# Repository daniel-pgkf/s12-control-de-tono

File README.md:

**Español** · [English](#english)

# S12 — Enseñar electrónica a través de equipos de música

S12 es un proyecto para enseñar electrónica usando como material de estudio los **equipos de música**: efectos, pedales, amplificadores, guitarras. La premisa es que un pedal de distorsión, una perilla de tono o una etapa de ganancia no son ejemplos decorativos de la teoría de circuitos — son teoría de circuitos, en un objeto que el estudiante ya conoce, ya escucha y ya quiere entender.

El proyecto tiene dos componentes que se alimentan mutuamente:

- **Los cursos** — material pedagógico completo y replicable, diseñado por audiencia.
- **El FRA** — un analizador de respuesta en frecuencia, construido desde cero, que sirve para caracterizar los efectos que ya existen y los que construyen los estudiantes, y para tocarlos con una guitarra eléctrica.

---

## El programa y sus cursos

S12 no es un curso único: es un programa del que se van derivando cursos, cada uno con su audiencia y su equipo de entrada. Lo que se mantiene constante es el método — entrar por un equipo de música real, construir la intuición antes de la fórmula, y cerrar midiendo.

### Curso 1 — Control de Tono

**Audiencia:** estudiantes de primer semestre de ingeniería electrónica, sin conocimientos previos de electrónica.

**Equipo de entrada:** la perilla de tono de una guitarra eléctrica.

Este primer curso es el que da nombre al repositorio. Su punto de entrada es la perilla de tono porque es, probablemente, el circuito no trivial más accesible que existe: se gira con la mano y el resultado se escucha de inmediato.

Una perilla de tono es un filtro RC pasa-bajos. Es un potenciómetro — girarla cambia el valor de la resistencia (R), lo que desplaza la frecuencia de corte del filtro y modifica el timbre de la guitarra. El capacitor es fijo. Ese objeto cotidiano contiene, en su interior, los mismos principios que se usan para diseñar filtros de audio, sistemas de comunicación y circuitos de procesamiento de señales.

**Progresión temática:**

```
Divisor de voltaje → Ley de mallas → Superposición → Filtros RC → Diagramas de Bode
```

Cada concepto se introduce como extensión natural del anterior. Al final, la perilla de tono deja de ser un misterio: el estudiante sabe exactamente qué está cambiando cuando la gira y por qué eso afecta el sonido.

**Formato:**

- Máximo 1.5 horas por sesión
- Entre 3 y 6 sesiones en total
- Cierra con un proyecto integrador en el que los estudiantes construyen o modifican un filtro RC y escuchan el resultado en tiempo real

### Cursos siguientes

El resto del gear musical queda como territorio por recorrer: distorsión y recorte, etapas de ganancia, delay, las fuentes de alimentación de un amplificador. Cada uno entra por su propio equipo y apunta a su propia audiencia. El curso de la perilla de tono es **el diseño para primeros semestres**, no el alcance del programa.

---

## Filosofía pedagógica

**Mínima matemática, máxima intuición.**

La idea es la misma que sigue Veritasium o 3Blue1Brown: el efecto se muestra antes de explicarse, la intuición se construye antes de formalizarse. Las fórmulas llegan al final, como descripción de algo que ya se entiende — no como punto de partida.

Para lograrlo se usa un sistema de analogías físicas. En lugar de definir el voltaje como diferencia de potencial eléctrico, se introduce como una propiedad del espacio que hace que una pelota —el portador de carga— siempre ruede de lo alto a lo bajo. En lugar de memorizar que un capacitor "bloquea DC y pasa AC", se visualiza como un bloque elástico que responde distinto según qué tan rápido lleguen las señales.

Estas analogías son deliberadamente imperfectas: son herramientas para construir intuición, no definiciones formales. El objetivo es que cuando el estudiante vea la definición real, ya tenga algo concreto en la cabeza a qué anclarla.

Un principio atraviesa todo el material: la resistencia le cobra **energía** a la carga, no existencia. La pelota nunca desaparece — si se queda sin energía se detiene, pero sigue ahí. Eso ataca de raíz la idea de que "la corriente se gasta".

---

## El FRA

### Qué es

Un **Frequency Response Analyzer** (analizador de respuesta en frecuencia) es un instrumento que mide cómo una red de dos puertos modifica una señal en función de la frecuencia. La salida es un diagrama de Bode: magnitud en dB y fase en grados, trazados sobre el eje de frecuencia.

Este FRA cubre el rango de 20 Hz a 20 kHz — el espectro audible completo.

### Para qué existe

El FRA es el instrumento de caracterización del programa. Se le conecta un efecto —uno comercial, uno casero, o **uno desarrollado por los estudiantes**— y mide qué le hace a la señal. En modo pedal, además, ese mismo efecto se puede **tocar con una guitarra eléctrica** en tiempo real.

Eso es lo que cierra el ciclo: el estudiante construye un efecto, lo mide y le ve el Bode, y lo toca. Sin el FRA, un efecto propio se queda en "suena raro". Con el FRA se vuelve un circuito caracterizado.

De ahí sale una restricción de diseño que no es negociable: el DUT (*device under test*) tiene que ser **genérico e intercambiable**. Cualquier efecto de un estudiante debe poder entrar, no solo una red RC. El slot modular y los jacks de 1/4" son parte del propósito, no un detalle de empaque.

### Cómo funciona

La señal entra por un jack, se acondiciona, y llega al slot donde está conectado el DUT. Lo que hace al FRA un instrumento de medida y no solo una caja de paso es que **mide los dos lados del DUT a la vez**: la señal tal como entra y la señal tal como sale. Comparar esas dos capturas es lo que da la respuesta en frecuencia.

Un microcontrolador se encarga de la captura, del cálculo y de enviar los datos al PC, donde se visualizan.

### Modos de operación

**Modo Pedal**

La señal de la guitarra pasa en vivo por el DUT y sale por el jack de salida, hacia un parlante o un amplificador. Mientras tanto se monitorean entrada y salida, así que el músico escucha el efecto y ve su huella espectral al mismo tiempo.

**Modo Bode**

Se desconecta la guitarra y se excita el DUT con una señal generada internamente. Comparando lo que entra con lo que sale, se obtiene el diagrama de Bode completo del efecto, de forma automática.

La excitación es ruido blanco: como tiene espectro plano, golpea todas las frecuencias del rango a la vez y la respuesta completa se obtiene en una sola captura corta, en lugar de barrer frecuencia por frecuencia. La estimación usa el método de Welch y reporta la coherencia como indicador de confiabilidad, para saber en qué bandas la medida es de fiar. El procesamiento está validado en `FRA/codigos/ruido_blanco.ipynb`.

---

## Las presentaciones

### Formato general

Las presentaciones no son slides. Son escenas continuas con checkpoints controlados por teclado: el instructor avanza cuando el grupo está listo, ni más rápido ni más lento. Varias escenas son además **simuladores** que el instructor maneja en vivo — se abre y cierra el circuito, se sueltan cargas, se cambia la resistencia, se transforma el modelo físico en esquemático.

Cada sesión combina dos tipos de contenido animado:

**Manim CE (Python)** — animaciones matemáticas y técnicas: ondas, diagramas de Bode emergiendo, circuitos con flechas, transformaciones. Renderizadas a video.

**p5.js (JavaScript)** — simulaciones físicas interactivas: la carga viajando por el conductor, el aceite de la resistencia deformándose a su paso, el divisor de voltaje respondiendo en tiempo real. Corren directo en el browser.

Un player web propio combina los clips de Manim y los sketches de p5.js en una sola secuencia navegable, y comparte una paleta única entre ambos mundos para que no se note la costura.

### Secuencia de cada concepto

Para cualquier concepto del curso, la presentación sigue siempre el mismo orden:

1. **Demostración observable** — se muestra el fenómeno antes de nombrarlo
2. **Analogía física animada** — se construye la intuición con el modelo físico
3. **Transferencia al circuito** — se mapea la analogía al circuito real
4. **Formalización** — llega la fórmula, ya anclada a algo concreto
5. **Medición** — se verifica con el FRA

---

## Stack técnico

| Herramienta         | Uso                                              |
| ------------------- | ------------------------------------------------ |
| Python 3.12 + venv  | Base del proyecto                                |
| Manim CE v0.20.1    | Animaciones técnicas y matemáticas             |
| p5.js (vendorizado) | Simulaciones físicas interactivas en browser    |
| FFmpeg              | Renderizado de video                             |
| Jupyter             | Documentación pedagógica y análisis de señal |
| KiCad               | Diseño de la PCB del FRA                        |

---

## Estructura del repositorio

```
control-de-tono/
├── presentaciones/     # Animaciones Manim, sketches p5.js, player web
├── FRA/                # Hardware, firmware, software PC
├── compras/            # BOM y materiales
└── syllabus/           # Contenido del curso, notebooks pedagógicos
```

Para correr las presentaciones:

```bash
cd presentaciones
python servidor.py 8000
# luego abrir http://127.0.0.1:8000/player/
```

<br>

---

[Español](#espanol) · **English**

# S12 — Teaching electronics through music gear

S12 is a project for teaching electronics using **music gear** as the study material: effects, pedals, amplifiers, guitars. The premise is that a distortion pedal, a tone knob or a gain stage aren't decorative examples of circuit theory — they *are* circuit theory, embodied in an object the student already knows, already listens to, and already wants to understand.

The project has two components that feed each other:

- **The courses** — complete, reproducible teaching material, designed per audience.
- **The FRA** — a frequency response analyzer, built from scratch, used to characterize both existing effects and the ones students build, and to play them through an electric guitar.

---

## The program and its courses

S12 isn't a single course: it's a program that spawns courses, each with its own audience and its own entry-point piece of gear. What stays constant is the method — enter through a real piece of music gear, build intuition before the formula, and close the loop by measuring.

### Course 1 — Tone Control

**Audience:** first-semester electronic engineering students, with no prior background in electronics.

**Entry-point gear:** the tone knob of an electric guitar.

This first course is the one the repository is named after. Its entry point is the tone knob because it's arguably the most accessible non-trivial circuit there is: you turn it by hand and hear the result immediately.

A tone knob is an RC low-pass filter. It's a potentiometer — turning it changes the resistance (R), which shifts the filter's cutoff frequency and alters the guitar's timbre. The capacitor is fixed. That everyday object contains, inside it, the same principles used to design audio filters, communication systems and signal processing circuits.

**Topic progression:**

```
Voltage divider → Kirchhoff's voltage law → Superposition → RC filters → Bode plots
```

Each concept is introduced as a natural extension of the previous one. By the end, the tone knob stops being a mystery: the student knows exactly what changes when they turn it, and why that affects the sound.

**Format:**

- 1.5 hours per session, maximum
- 3 to 6 sessions total
- Closes with a capstone project where students build or modify an RC filter and hear the result in real time

### Later courses

The rest of the musical gear landscape is territory still to be covered: distortion and clipping, gain stages, delay, amplifier power supplies. Each one enters through its own piece of gear and targets its own audience. The tone knob course is **the design for first-semester students**, not the scope of the program.

---

## Teaching philosophy

**Minimum math, maximum intuition.**

The approach is the one Veritasium and 3Blue1Brown follow: show the effect before explaining it, build the intuition before formalizing it. Formulas arrive last, as a description of something already understood — not as the starting point.

To get there, the material uses a system of physical analogies. Instead of defining voltage as electric potential difference, it's introduced as a property of space that makes a ball — the charge carrier — always roll from high to low. Instead of memorizing that a capacitor "blocks DC and passes AC", it's visualized as an elastic block that responds differently depending on how fast the signals arrive.

These analogies are deliberately imperfect: they're tools for building intuition, not formal definitions. The goal is that when the student meets the real definition, they already have something concrete to anchor it to.

One principle runs through all the material: resistance charges the carrier **energy**, not existence. The ball never disappears — if it runs out of energy it stops, but it's still there. That attacks the "current gets used up" misconception at its root.

---

## The FRA

### What it is

A **Frequency Response Analyzer** is an instrument that measures how a two-port network modifies a signal as a function of frequency. The output is a Bode plot: magnitude in dB and phase in degrees, plotted against frequency.

This FRA covers 20 Hz to 20 kHz — the full audible spectrum.

### Why it exists

The FRA is the program's characterization instrument. You plug an effect into it — a commercial one, a homemade one, or **one developed by the students** — and it measures what that effect does to the signal. In pedal mode, that same effect can also be **played through an electric guitar** in real time.

That's what closes the loop: the student builds an effect, measures it and sees its Bode plot, and then plays it. Without the FRA, a homemade effect stays at "sounds weird". With the FRA it becomes a characterized circuit.

From this follows a non-negotiable design constraint: the DUT (device under test) must be **generic and swappable**. Any student's effect has to be able to go in, not just an RC network. The modular slot and the 1/4" jacks are part of the purpose, not a packaging detail.

### How it works

The signal comes in through a jack, gets conditioned, and reaches the slot where the DUT is connected. What makes the FRA a measuring instrument rather than just a box the signal passes through is that it **measures both sides of the DUT at once**: the signal as it goes in and the signal as it comes out. Comparing those two captures is what yields the frequency response.

A microcontroller handles capture, computation, and streaming the data to the PC, where it's visualized.

### Operating modes

**Pedal mode**

The guitar signal passes live through the DUT and out the output jack, into a speaker or an amplifier. Meanwhile input and output are monitored, so the player hears the effect and sees its spectral fingerprint at the same time.

**Bode mode**

The guitar is disconnected and the DUT is excited with an internally generated signal. Comparing what goes in with what comes out yields the effect's complete Bode plot, automatically.

The excitation is white noise: since its spectrum is flat, it hits every frequency in the range at once, so the full response comes from a single short capture instead of a frequency-by-frequency sweep. The estimate uses Welch's method and reports coherence as a confidence indicator, to tell which bands are trustworthy. The processing is validated in `FRA/codigos/ruido_blanco.ipynb`.

---

## The presentations

### General format

The presentations aren't slides. They're continuous scenes with keyboard-driven checkpoints: the instructor advances when the group is ready, no faster and no slower. Several scenes are also **simulators** the instructor drives live — opening and closing the circuit, releasing charges, swapping the resistance, morphing the physical model into a schematic.

Each session combines two kinds of animated content:

**Manim CE (Python)** — mathematical and technical animations: waveforms, Bode plots being drawn, circuits with annotation arrows, transformations. Rendered to video.

**p5.js (JavaScript)** — interactive physical simulations: the charge traveling down the conductor, the resistance's oil deforming as it passes, the voltage divider responding in real time. They run directly in the browser.

A custom web player stitches the Manim clips and p5.js sketches into a single navigable sequence, and shares one palette across both worlds so the seam doesn't show.

### Sequence for every concept

For any concept in the course, the presentation always follows the same order:

1. **Observable demonstration** — show the phenomenon before naming it
2. **Animated physical analogy** — build intuition with the physical model
3. **Transfer to the circuit** — map the analogy onto the real circuit
4. **Formalization** — the formula arrives, already anchored to something concrete
5. **Measurement** — verify it with the FRA

---

## Tech stack

| Tool                | Used for                                     |
| ------------------- | -------------------------------------------- |
| Python 3.12 + venv  | Project base                                 |
| Manim CE v0.20.1    | Technical and mathematical animations        |
| p5.js (vendored)    | Interactive physical simulations in-browser  |
| FFmpeg              | Video rendering                              |
| Jupyter             | Teaching documentation and signal analysis   |
| KiCad               | FRA PCB design                               |

---

## Repository layout

```
control-de-tono/
├── presentaciones/     # Manim animations, p5.js sketches, web player
├── FRA/                # Hardware, firmware, PC software
├── compras/            # BOM and materials
└── syllabus/           # Course content, teaching notebooks
```

To run the presentations:

```bash
cd presentaciones
python servidor.py 8000
# then open http://127.0.0.1:8000/player/
```

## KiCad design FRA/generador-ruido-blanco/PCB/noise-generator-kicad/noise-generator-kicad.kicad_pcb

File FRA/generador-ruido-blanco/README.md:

# Generador de ruido blanco — verificación de planicidad

Mide el espectro **real** del generador de ruido blanco del FRA, capturándolo por
la Scarlett 2i2. Es la contraparte física de [`../codigos/ruido_blanco.ipynb`](../codigos/ruido_blanco.ipynb),
que simula el ruido con `randn()` y establece la teoría.

## Cadena de medición

```
Generador ruido blanco → jack 1/4" → Scarlett 2i2 (line in) → USB → captura_planicidad.py
```

Antes de correr: phantom power **apagado**, ganancia ajustada sin clipping.

## El generador — diseño final

Fuente de ruido por **avalancha**: la juntura base-emisor del transistor en
inversa, polarizada por el 100K desde 12 V. Acople de 1 µF y pulldown de 100K
(pasaaltos en 1.6 Hz, bien debajo de la banda).

```
        12V
         │
        100K
         │        1µF                                            1K
  Q ─────●────────┤├────●──── [buffer] ── [G=15.5] ── [G=15.5] ── [buffer] ──/\/\── NOISE
  (BE en                │
   inversa)           100K
         │              │
        GND            GND
```

Cuatro amplificadores en **un solo TL074** (JFET, quad, GBW 3 MHz):

| Etapa | Función | Rf / R1 | Ganancia |
|---|---|---|---|
| 1 | buffer de entrada | — | 1 |
| 2 | ganancia, no inversor | 680k / 47k | 15.47 |
| 3 | ganancia, no inversor | 680k / 47k | 15.47 |
| 4 | buffer de salida | — | 1 |

**Ganancia total: 15.47² ≈ 239.** Entrada ~0.84 mV RMS → salida ~200 mV RMS,
que es nivel de humbucker (ver "Nivel de salida" abajo).

### Por qué la ganancia va repartida y no en una etapa

Esta es **la** decisión de diseño del circuito, y no es obvia. Un opamp no
entrega su ganancia a cualquier frecuencia: lo constante es el **producto**
ganancia-ancho de banda. El ancho de banda real de una etapa es `GBW / G`.

La primera versión eran `1 + 100k/680 = 148` en una sola etapa:

```
fc = 3 MHz / 148 = 20.3 kHz      →  el polo caía justo en el borde de la banda
```

Repartida en dos etapas de 15.47, cada una solo necesita `3 MHz / 15.47`:

```
fc_etapa  = 194 kHz
fc_total  = 194 kHz × √(2^(1/2) − 1) = 125 kHz
```

(El `fc_total` no es el de una etapa: al encadenar N polos iguales, el −3 dB
conjunto llega antes. Con N=2 el factor es 0.644.)

Error en 20 kHz: **−0.09 dB**, contra −2.95 dB de la versión de una etapa. Y eso
que la ganancia total *subió* de 148 a 239: repartida, sale gratis.

> **Honestidad sobre la causa:** el polo de GBW explica ~3 dB, pero la versión
> vieja medía ~19 dB de rango. El resto salía del nodo de 50 kΩ sin bufferear
> (y de un opamp viejo que nunca identificamos). Los dos cambios —repartir la
> ganancia y bufferear la entrada— se hicieron juntos, así que con una sola
> medición no se pueden separar. Ambos eran necesarios.

### Por qué los buffers

- **Entrada:** el nodo de ruido tiene 100k ‖ 100k = **50 kΩ** de impedancia. Con
  esa Z, cualquier capacidad parásita del protoboard forma su propio pasabajos,
  y un opamp bipolar además metería offset por corriente de polarización. El
  buffer JFET (Ib ≈ 30 pA) aísla el nodo y manda ese polo lejos.
- **Salida:** deja el generador con impedancia baja para manejar el cable sin
  que la capacidad se coma los agudos. El 1K en serie es protección.

> Si algún día se sube la ganancia, **repartirla** — no subir una etapa. Al
> triplicar G se te divide por tres el ancho de banda de esa etapa.

### Nivel de salida

Ajustado a **~200 mV RMS** para imitar una pastilla pasiva (humbucker típica:
150–350 mV RMS). Con ruido gaussiano se iguala el **RMS, no el Vpp** — los picos
del ruido son estadísticos y crecen con el tiempo de observación, así que no hay
un Vpp definido. Con factor de cresta ≈ 4 (12 dB), esos 200 mV dan picos de
~800 mV.

> **Cuidado al medir la entrada con osciloscopio:** los ~0.84 mV RMS del nodo de
> ruido están por debajo del piso de un scope típico. Si lees ~20 mV ahí, es casi
> seguro el ruido propio del instrumento, no la señal. La cuenta que cierra es:
> salida medida ÷ 239.

## Uso

```bash
python captura_planicidad.py --list     # ver dispositivos, identificar la Scarlett
python captura_planicidad.py            # captura 10 s y analiza (autodetecta Scarlett)
python captura_planicidad.py --device 3 --dur 10 --channel 1
python captura_planicidad.py --wav espectro_ruido.wav   # re-analizar sin recapturar
```

Cada captura guarda el audio crudo en `.wav` junto al `.png`, así se puede
re-analizar con otro `nperseg` sin volver a montar el setup.

## Qué hace

1. **Verifica clipping** antes de procesar — aborta si el pico llega a fondo de
   escala. Un factor de cresta bajo (< 8 dB) también delata clipping: el ruido
   gaussiano sano da ≈ 11–13 dB.
2. **PSD por Welch**, no FFT directa. Una sola ventana de ruido tiene ~5.6 dB de
   desviación por bin (chi² 2 gdl) — imposible distinguir la respuesta del
   generador de la varianza de la propia realización. Welch promedia ventanas
   solapadas y baja esa varianza.
3. **Métricas de planicidad** en 20 Hz – 20 kHz: nivel medio, desviación estándar,
   rango max-min y SFM.

## Antes de medir: poner la Scarlett a 48 kHz

Estado al 2026-07-14: la interfaz está configurada a **44.1 kHz** en Windows, y
el script aborta con instrucciones si se pide 48 kHz. Conviene cambiarla:

> Panel de control de sonido → Grabación → Scarlett 2i2 → Propiedades →
> Opciones avanzadas → 48000 Hz

**Por qué importa:** a 44.1 kHz el Nyquist es 22.05 kHz, así que el filtro
anti-alias del ADC empieza a caer justo sobre los 20 kHz que queremos medir —
se mediría el filtro de la Scarlett, no el generador. A 48 kHz el Nyquist es
24 kHz y deja margen.

El script usa **WASAPI** a propósito. MME y DirectSound aceptan cualquier
sample rate, pero lo hacen remuestreando en silencio, lo que mete su propio
rolloff. WASAPI en modo compartido rechaza el rate que no coincide — un error
explícito es preferible a un espectro falso.

## Zumbido de 60 Hz

El script mide el hum aparte de la planicidad y lo reporta en su propia sección,
con el exceso en dB de cada armónico sobre el piso de ruido local.

### Por qué se mide aparte en vez de filtrarlo

El hum es de **banda angosta** (60 Hz y armónicos) y el ruido blanco es de
**banda ancha**. Son separables, y conviene separarlos en vez de mezclarlos:

- **Un notch no sirve** para esta métrica: borra el hum, pero deja un hueco que
  la estadística de planicidad lee como una caída del generador. Estarías
  midiendo tu propio filtro.
- **Excluir los bins contaminados** de la estadística mide lo que querés saber
  (¿es plano el ruido de banda ancha?) sin mentir sobre el resto. El hum se
  reporta por separado, con su nivel real.

El script excluye sólo las líneas que sobresalen > 3 dB del piso, y busca
armónicos hasta 2 kHz nada más — el acople de red decae rápido, y arriba de eso
los armónicos de 60 Hz caen más juntos que la resolución de Welch, así que
buscarlos marcaría casi todos los bins como "red".

Cuánto pesa: en una prueba con hum inyectado a propósito (60/120/180 Hz), el
rango pasó de **21.6 dB con hum a 4.1 dB sin él**. El hum solo destroza la
métrica de rango.

### Cómo bajarlo — de más probable a menos

1. **Lazo de tierra (lo más probable, y gratis de probar).** La Scarlett se
   alimenta por USB de la laptop. Si la laptop está enchufada, tenés dos caminos
   a tierra y la diferencia entre ellos aparece como 60 Hz.
   → **Desenchufá el cargador y medí con la laptop a batería.** Si el hum cae,
   era esto.
2. **Alimentá el generador con pila de 9 V**, no con fuente de pared. Elimina de
   una el ripple de la fuente y el lazo de tierra. Para un generador casero es
   lo más efectivo por lo que cuesta.
3. **Cable corto y blindado**, con la malla a tierra en **un solo extremo** (si
   se conecta en los dos, la malla misma se vuelve una espira de tierra).
4. **Alejá el generador** de fuentes conmutadas, transformadores, cargadores,
   monitores y tubos fluorescentes/dimmers. Mover 30 cm a veces ya se nota.
5. **Tierra en estrella** en el protoboard: todos los retornos a un punto, no
   encadenados. Trenzá los cables de alimentación y separalos de los de señal.
6. **Usá la entrada LINE, no la de instrumento (Hi-Z)** — la Hi-Z tiene mucha
   más impedancia y capta bastante más.

### Diagnóstico: ¿de dónde viene?

Cuatro capturas cortas (`--dur 2`) aíslan el origen. Cada `.wav` queda guardado:

| # | Setup | Si aparece el hum acá... |
|---|---|---|
| A | Nada conectado a la Scarlett | es la interfaz / el USB |
| B | Cable conectado, otro extremo al aire | el cable hace de antena → blindaje |
| C | Cable al generador, generador apagado | es la tierra / la fuente del generador |
| D | Generador encendido | lo que quede es del circuito en sí |

```bash
python captura_planicidad.py --dur 2 --out A_nada.png
python captura_planicidad.py --dur 2 --out B_cable_al_aire.png
python captura_planicidad.py --dur 2 --out C_gen_apagado.png
python captura_planicidad.py --dur 2 --out D_gen_on.png
```

Comparás el exceso en 60 Hz que reporta cada una y sabés dónde atacar.

### Para mirar el hum en detalle: `--nperseg 16384`

```bash
python captura_planicidad.py --wav espectro_ruido.wav --nperseg 16384
```

El default (4096) da 11.7 Hz/bin, pensado para promediar mucho y medir
planicidad. Es poca resolución para las líneas de red: en la prueba con hum
inyectado, 4096 detectó 60/120/180 Hz pero **se perdió el armónico de 300 Hz**,
que 16384 (2.9 Hz/bin) sí encontró. También sube el exceso reportado en 60 Hz de
+19.2 a +25.3 dB, más cerca del valor real — a poca resolución la energía del
tono se reparte entre bins y se subestima.

Dos herramientas distintas: **4096 para planicidad, 16384 para cazar hum.** El
`.wav` queda guardado, así que se reanaliza sin volver a medir.

> **Límite:** el exceso en dB de una línea depende de `nperseg` (la PSD de una
> senoide crece con la resolución; la del ruido no). Compará capturas con el
> mismo `nperseg`, no entre distintos. Y a 11.7 Hz/bin, 50 y 60 Hz caen a un bin
> de distancia: son indistinguibles sin subir la resolución.

> **Buena noticia para el FRA:** el hum molesta para *verificar el generador*,
> pero mucho menos para el Bode. Como `H(f) = ADC₂(f)/ADC₁(f)`, un hum común a
> los dos canales se cancela en gran parte al dividir. Además la coherencia
> (γ²) cae en 60 Hz y te avisa sola de que ese punto no es confiable.

## Umbrales

| Métrica | Referencia | Origen |
|---|---|---|
| Desv. estándar | < 3 dB | aceptable para audio |
| Rango max-min | < 6 dB | peor pico/valle tolerable |
| SFM | > −1 dB | 0 dB = plano ideal |
| Hum sobre el piso | < 10 dB | líneas de red (se mide aparte) |

## Piso del estimador

Con ruido gaussiano ideal (10 s, `nperseg=4096`, 233 ventanas) el script mide
**std 0.29 dB, rango 1.93 dB, SFM −0.01 dB**. Ese es el piso del método: cualquier
desviación mayor medida en el generador real es del generador o de la interfaz,
no del estimador.

## Resultados medidos

| | 1 etapa de 148, sin buffers | **2 etapas de 15.47 + buffers** | Piso ideal |
|---|---|---|---|
| std | 4.38 dB | **0.58 dB** ✓ | 0.29 dB |
| rango | 19.46 dB | **4.69 dB** ✓ | 1.93 dB |
| SFM | −2.29 dB | **−0.04 dB** ✓ | −0.01 dB |
| hum 60 Hz | +3.4 dB | +4.0 dB | — |
| nivel medio | −71.8 dB/Hz | −76.8 dB/Hz | — |

(El **nivel medio no es comparable** entre capturas: depende de dónde esté la
perilla de ganancia de la Scarlett. Solo la *forma* de la curva —std, rango,
SFM— es independiente de la ganancia, y por eso son esas las métricas.)

El SFM es el dato que cierra el caso: pasó de −2.29 a −0.04, prácticamente el
ideal. Como el SFM es lo más sensible a una inclinación de banda ancha, ese
número dice que el polo se eliminó, no que se tapó.

**Lo que quedó, y no vale la pena perseguir:**

- El **hum es ahora el factor limitante** del rango, no el generador. El bulto de
  180 Hz queda a +2.8 dB de la media — justo debajo del umbral de 3 dB, así que
  no se excluye y cuenta en el rango. Sin él, el rango bajaría a ~3 dB.
- La caída de ~1.5 dB entre 10k y 20k puede ser en buena parte el filtro
  anti-alias de la propia Scarlett, no el generador.
- **SNR:** señal a −76.8 dB/Hz contra un piso de interfaz de −148.7 dB/Hz
  (medido sin nada conectado) = **~72 dB de margen** en toda la banda.

> Recordá que esta planicidad ni siquiera era necesaria: `H(f) = ADC₂/ADC₁` la
> cancela al dividir. Lo que se compró es **SNR parejo** en toda la banda.

## Trade-off de `nperseg`

Con 10 s a 48 kHz:

| nperseg | Resolución | Ventanas | Espectro |
|---|---|---|---|
| 2048 | 23.4 Hz | ~468 | más suave, menos detalle |
| **4096** | **11.7 Hz** | **~233** | equilibrio (default) |
| 8192 | 5.9 Hz | ~117 | más detalle, más rugoso |

Más resolución cuesta ventanas de promedio. Para *planicidad* conviene
priorizar el promedio; 4096 ya da 11.7 Hz, de sobra para ver desviaciones de
banda ancha.

> **Nota:** una irregularidad del generador no invalida el Bode del FRA —
> `H(f) = ADC₂(f)/ADC₁(f)` cancela lo que sea común a ambos canales. Lo que
> importa es que haya SNR suficiente en toda la banda.

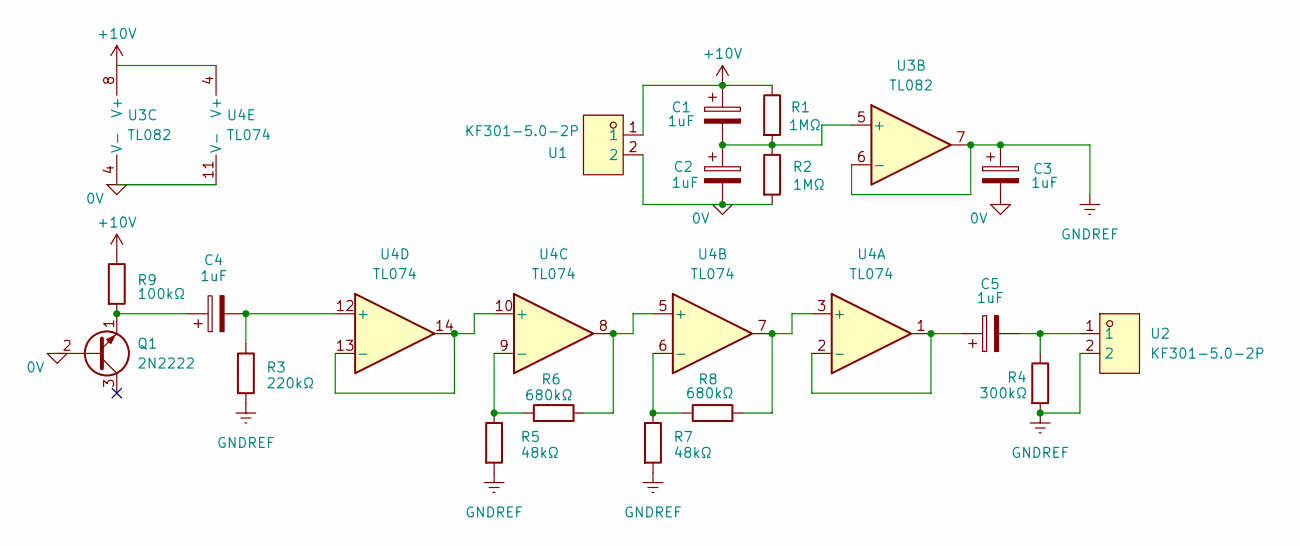
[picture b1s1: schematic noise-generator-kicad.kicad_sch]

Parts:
C1, C2, C3, C4, C5: 1uF; CP_Radial_D5.0mm_P2.00mm
Q1: 2N2222; TO-92L_Inline_Wide
R1, R2: 1MΩ; R_Axial_DIN0207_L6.3mm_D2.5mm_P7.62mm_Horizontal
R3: 220kΩ; R_Axial_DIN0207_L6.3mm_D2.5mm_P7.62mm_Horizontal
R4: 300kΩ; R_Axial_DIN0207_L6.3mm_D2.5mm_P7.62mm_Horizontal
R5, R7: 48kΩ; R_Axial_DIN0207_L6.3mm_D2.5mm_P7.62mm_Horizontal
R6, R8: 680kΩ; R_Axial_DIN0207_L6.3mm_D2.5mm_P7.62mm_Horizontal
R9: 100kΩ; R_Axial_DIN0207_L6.3mm_D2.5mm_P7.62mm_Horizontal
U1, U2: KF301-5.0-2P; CONN-TH_P5.00_KF301-5.0-2P; MPN KF301-5.0-2P; LCSC Part C474881
U3: TL082; DIP-8_W7.62mm_LongPads
U4: TL074; DIP-14_W7.62mm_LongPads

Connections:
0V: C2.2, C3.2, Q1.2 (B), R2.2, U1.2, U3.4 (V-), U4.11 (V-)
+10V: C1.1, R1.1, R9.1, U1.1, U3.8 (V+), U4.4 (V+)
GNDREF: C3.1, R3.2, R4.2, R5.2, R7.2, U2.2, U3.6 (-), U3.7
unnamed: C5.2, R4.1, U2.1
unnamed: C4.1, Q1.1 (E), R9.2
unnamed: C1.2, C2.1, R1.2, R2.1, U3.5 (+)
unnamed: R8.2, U4.3 (+), U4.7
unnamed: C5.1, U4.1, U4.2 (-)
unnamed: R6.2, U4.5 (+), U4.8
unnamed: R7.1, R8.1, U4.6 (-)
unnamed: U4.10 (+), U4.13 (-), U4.14
unnamed: R5.1, R6.1, U4.9 (-)
unnamed: C4.2, R3.1, U4.12 (+)

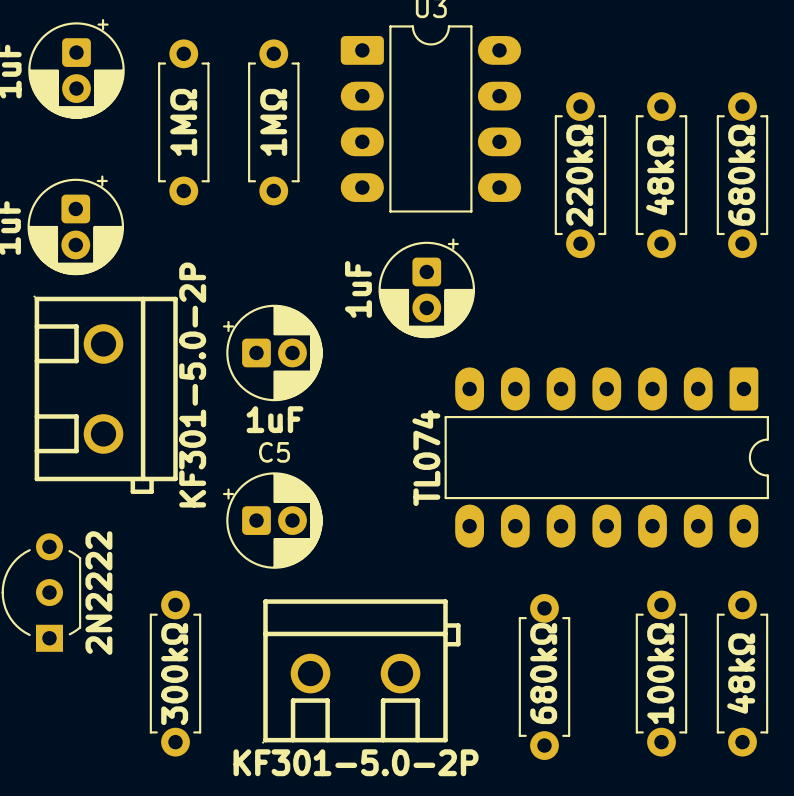
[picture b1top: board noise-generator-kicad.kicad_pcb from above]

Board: 2 copper layers, 19 parts (0 on the bottom side), 13 nets.

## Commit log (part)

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2026-05-12 commit inicial
2026-05-12 readme
2026-05-12 arreglo readme
